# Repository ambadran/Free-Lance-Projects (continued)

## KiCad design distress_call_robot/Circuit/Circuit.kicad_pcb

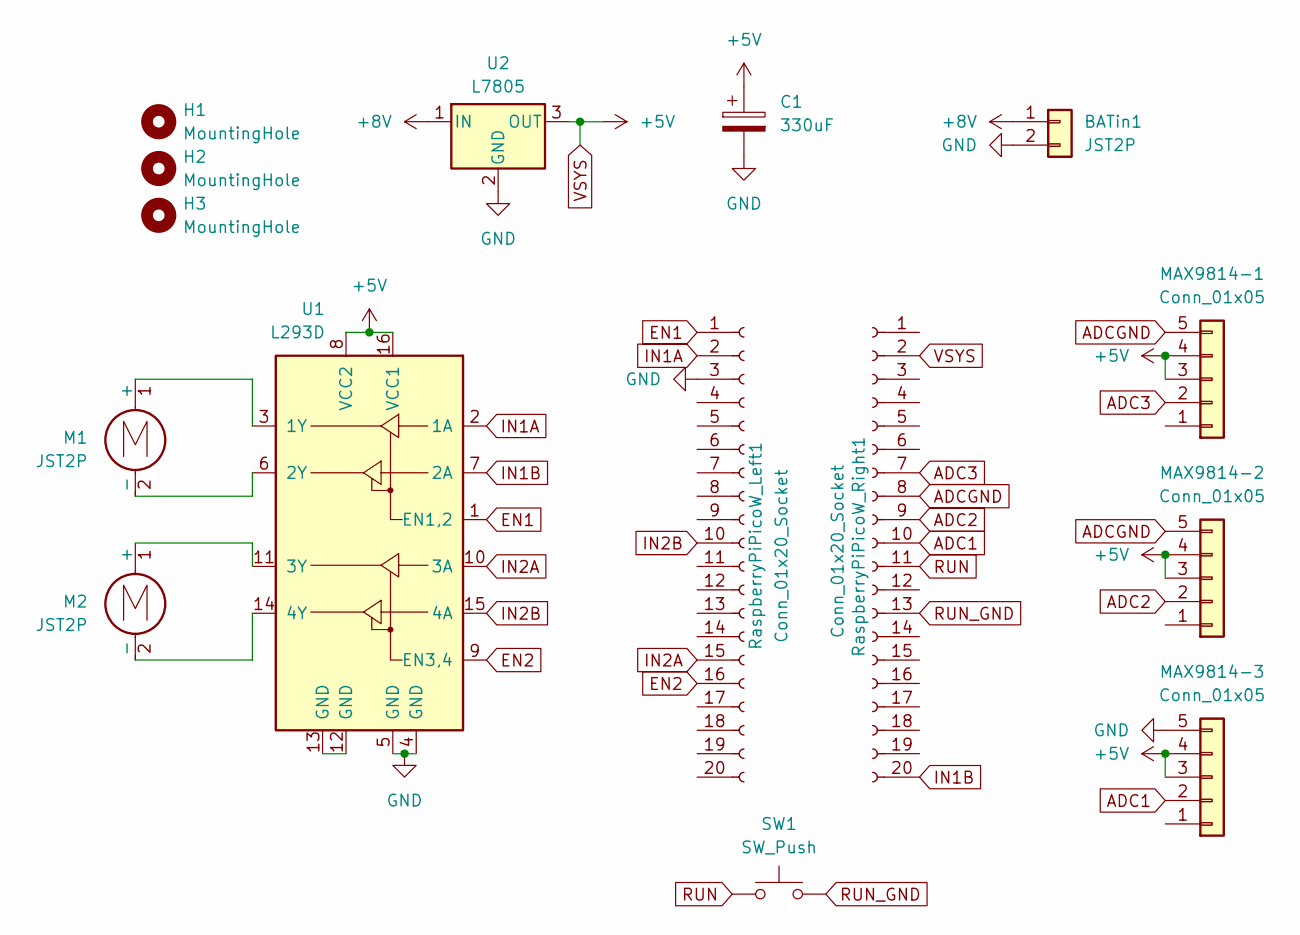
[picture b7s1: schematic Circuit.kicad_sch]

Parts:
BATin1: JST2P; JST_EH_B2B-EH-A_1x02_P2.50mm_Vertical
C1: 330uF; CP_Radial_D6.3mm_P2.50mm
H1, H2, H3: MountingHole; MountingHole_3.2mm_M3_DIN965_Pad
M1, M2: JST2P; JST_EH_B2B-EH-A_1x02_P2.50mm_Vertical
MAX9814-1, MAX9814-2, MAX9814-3: Conn_01x05; PinSocket_1x05_P2.54mm_Vertical
RaspberryPiPicoW_Left1: Conn_01x20_Socket; PinHeader_1x20_P2.54mm_Vertical
RaspberryPiPicoW_Right1: Conn_01x20_Socket; PinHeader_1x20_P2.54mm_Vertical
SW1: SW_Push; R_Axial_DIN0204_L3.6mm_D1.6mm_P5.08mm_Vertical
U1: L293D; DIP-16_W7.62mm_Socket_LongPads
U2: L7805; TO-220-3_Vertical

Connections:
+8V: BATin1.1, U2.1 (IN)
ADC1: MAX9814-3.2, RaspberryPiPicoW_Right1.10
ADC2: MAX9814-2.2, RaspberryPiPicoW_Right1.9
ADC3: MAX9814-1.2, RaspberryPiPicoW_Right1.7
ADCGND: MAX9814-1.5, MAX9814-2.5, RaspberryPiPicoW_Right1.8
EN1: RaspberryPiPicoW_Left1.1, U1.1 (EN1,2)
EN2: RaspberryPiPicoW_Left1.16, U1.9 (EN3,4)
GND: BATin1.2, C1.2, MAX9814-3.5, RaspberryPiPicoW_Left1.3, U1.4 (GND), U1.5 (GND), U2.2 (GND)
IN1A: RaspberryPiPicoW_Left1.2, U1.2 (1A)
IN1B: RaspberryPiPicoW_Right1.20, U1.7 (2A)
IN2A: RaspberryPiPicoW_Left1.15, U1.10 (3A)
IN2B: RaspberryPiPicoW_Left1.10, U1.15 (4A)
unnamed: M1.1 (+), U1.3 (1Y)
unnamed: M1.2 (-), U1.6 (2Y)
unnamed: M2.1 (+), U1.11 (3Y)
unnamed: M2.2 (-), U1.14 (4Y)
unnamed: U1.12 (GND), U1.13 (GND)
RUN: RaspberryPiPicoW_Right1.11, SW1.1
RUN_GND: RaspberryPiPicoW_Right1.13, SW1.2
VSYS: C1.1, MAX9814-1.3, MAX9814-1.4, MAX9814-2.3, MAX9814-2.4, MAX9814-3.3, MAX9814-3.4, RaspberryPiPicoW_Right1.2, U1.8 (VCC2), U1.16 (VCC1), U2.3 (OUT)

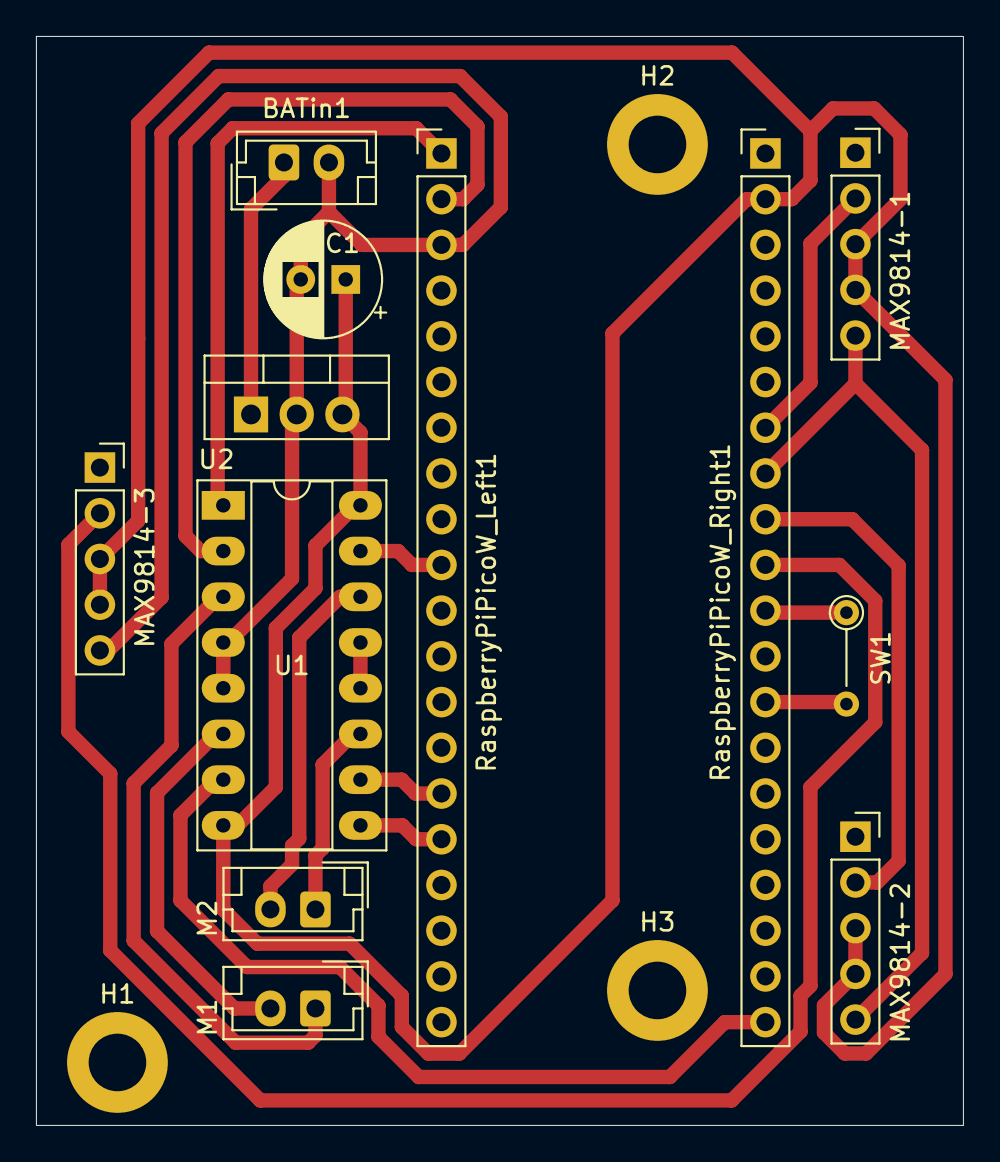
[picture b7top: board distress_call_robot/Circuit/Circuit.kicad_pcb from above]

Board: 2 copper layers, 51.5 x 60.5 mm, 15 parts (0 on the bottom side), 20 nets.

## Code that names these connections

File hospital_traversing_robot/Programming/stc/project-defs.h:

#ifndef PROJECT_DEFS_H
#define PROJECT_DEFS_H

/* gpio-hal Settings */
#define EnA_PORT GPIO_PORT2 // initiated by advpwm
#define EnA_PIN GPIO_PIN1  // initiated by advpwm
#define EnB_PORT GPIO_PORT3  // initiated by advpwm
#define EnB_PIN GPIO_PIN4  // initiated by advpwm
#define IN1_PORT GPIO_PORT2
#define IN1_PIN GPIO_PIN0
#define IN2_PORT GPIO_PORT3
#define IN2_PIN GPIO_PIN7
#define IN3_PORT GPIO_PORT3
#define IN3_PIN GPIO_PIN5
#define IN4_PORT GPIO_PORT3
#define IN4_PIN GPIO_PIN6

#define NRF24_CSN_PORT GPIO_PORT2 
#define NRF24_CSN_PIN GPIO_PIN2
#define NRF24_MOSI_PORT GPIO_PORT2  // iniated by spi-hal
#define NRF24_MOSI_PIN GPIO_PIN3  // iniated by spi-hal
#define NRF24_MISO_PORT GPIO_PORT2  // iniated by spi-hal
#define NRF24_MISO_PIN GPIO_PIN4  // iniated by spi-hal
#define NRF24_SCLK_PORT GPIO_PORT2  // iniated by spi-hal
#define NRF24_SCLK_PIN GPIO_PIN5  // iniated by spi-hal
#define NRF24_CE_PORT GPIO_PORT2  
#define NRF24_CE_PIN GPIO_PIN6  

#define HCSR04_TRIGGER_PORT GPIO_PORT3
#define HCSR04_TRIGGER_PIN GPIO_PIN2
#define HCSR04_ECHO_PORT GPIO_PORT3
#define HCSR04_ECHO_PIN GPIO_PIN3

#define NEO_M8N_PORT GPIO_PORT1
#define NEO_M8N_RX_PIN GPIO_PIN0
#define NEO_M8N_TX_PIN GPIO_PIN1

#define LED_PORT GPIO_PORT1
#define LED_PIN GPIO_PIN3

/* uart-hal Settings */
#define HAL_UARTS 2
#define UART2_RX_BUFFER_SIZE 233 //MUST DO THIS TO RECEIVE ALL NMEA STATEMENT!

#define CONSOLE_SPEED 250000
#define CONSOLE_UART UART1
#define CONSOLE_PIN_CONFIG 0  // TX->P3.1, RX->P3.0

#define NEO_M8N_UART_SPEED 9600
#define NEO_M8N_UART UART2
#define NEO_M8N_UART_PIN_CONFIG 0  // TX->P1.1, RX->P1.0

/* pwm Settings */
#define HAL_PWM_CALCULATE_PARAMETERS
#define HAL_PWM_NO_COUNTER_INT_HANDLER
#define HAL_PWM_NO_CHANNEL_INT_HANDLER
// EnA pin is P2.1/PWM1N_2
#define PWM_MOTOR_RIGHT_COUNTER PWM_COUNTER_A
#define PWM_MOTOR_RIGHT_CHANNEL PWM_Channel0
#define PWM_MOTOR_RIGHT_PIN_CONFIG 1
#define PWM_MOTOR_RIGHT_OUTPUT_MODE PWM_OUTPUT_N_ONLY 
// EnB in is P3.4/PWM4P_4/PWM8_2
#define PWM_MOTOR_LEFT_COUNTER PWM_COUNTER_B
#define PWM_MOTOR_LEFT_CHANNEL PWM_Channel7
#define PWM_MOTOR_LEFT_PIN_CONFIG 1
#define PWM_MOTOR_LEFT_OUTPUT_MODE PWM_OUTPUT_P_ONLY


/* timer-hal configs */
#define HAL_TIMER_API_STOP_TIMER
// Timer assignments
#define GLOBAL_TIMER TIMER0
#define GLOBAL_TIMER_ISR timer0_isr
#define GLOBAL_TIMER_INTERRUPT TIMER0_INTERRUPT
// TIMER1 is used for CONSOLE_UART
#define NEO_M8N_TIMER UART_USE_OWN_TIMER // TIMER2 is used for UART2
#define HCSR04_TIMER TIMER4
#define HCSR04_TIMER_ISR timer4_isr
#define HCSR04_TIMER_INTERRUPT TIMER4_INTERRUPT

/* external pin interrupts */
#define HCSR04_INT_PIN_ISR extint1_isr  // ECHO Pin, P3.3
#define HCSR04_INT_PIN_INTERRUPT EXTINT1_INTERRUPT // ECHO Pin, P3.3

/* SPI settings */
#define SPI_PIN_CONFIG 1
/* #define SPI_SPEED 8000000 */
#define SPI_SPEED 4000000UL

/* I2C settings */
#define CHOOSEN_I2C_PIN_SWITCH 0

/* nRF24L01 settings */
//#define NRF_DEBUGGING  //uncomment to print all the nrf24l01 registers after setting them with nrf24_device()
#define RF_CHANNEL_DEFAULT 46

/* HC05 Sensor Settings*/
#define ULTRASONIC_DEBUG
#define HCSR04_TIMER_COUNTER_TO_CM  233 //TODO: actually calculate and get this value
#define HCSR04_READ_PERIOD_MS 500


/* MPU6050 Settings */
// #define TEST_MPU_ACCEL  // If this setting is enabled the MCU will do nothing but keep printing the MPU values
// #define TEST_MPU_GYRO
#define ACCEL_SCALE 1000  // fixed-point value instead of floating point, 
#define ACCEL_SENSITIVITY ACCEL_SENSITIVITY_0  // 16-bit range is divided into max 2g
#define GYRO_SENSITIVITY GYRO_SENSITIVITY_0  // 16-bit range is divided into max 500deg/sec
//TODO: These values are set in place and no calibration routine yet
#define DEFAULT_ACCEL_OFFSET_X 0
#define DEFAULT_ACCEL_OFFSET_Y 0
#define DEFAULT_ACCEL_OFFSET_Z 0
//NOTE: gyro offset is calculated with every power up using a calibration routine
#define DEFAULT_GYRO_OFFSET_X 0
#define DEFAULT_GYRO_OFFSET_Y 0
#define DEFAULT_GYRO_OFFSET_Z 0
#define GYRO_CALIBRATION_SAMPLES 1000
#define GYRO_DT 10

/* HMC5883L settings */
/* #define TEST_MPU_MAG */
#define DEFAULT_MAG_GAIN HMC5883L_GAIN_1090
#define DEFAULT_MAG_OFFSET_X 0
#define DEFAULT_MAG_OFFSET_Y 0
#define DEFAULT_MAG_OFFSET_Z 0

/* NEO M8N Settings */

/* Differential Control Settings */
#define CM_TO_MOVEMENT_MS 15  // 1cm is moved in CM_TO_MOVEMENT_MS
#define DEGREE_TO_MOVEMENT_MS 3 // 1 degree is moved in DEGREE_TO_MOVEMENT_MS
#define PWM_MOTOR_FREQ 10000
#define DEFAULT_PWM_DUTY_CYCLE 50000  // The range is (0-2^16)

/* Orientation HAL settings */
#define COMP_FILTER_DT 30
#define COMP_FILTER_ALPHA 30  // %
#define COMP_FILTER_BETA  (100-COMP_FILTER_ALPHA) 
// Getting the orientation can be done through multitude of ways.
// for example roll could be derived from only accelerometer or only gyroscope or sensor fuse both
// The next setting specifies how each orientation: ROLL, PITCH, YAW is derived
// This allows flexible orientation aquiring and test the different advantages of each method
#define orientation_get_roll_deg get_accel_roll_deg
#define orientation_get_pitch_deg get_accel_pitch_deg
#define orientation_get_yaw_deg get_gyro_yaw_deg
// very important if no absolute yaw measurement procedure is implemented
#define STARTING_YAW_VALUE WEST
#define YAW_MULTIPLE_COMPENSATE 2.5

/* Closed loop Control Settings */
#define TOTAL_ORIENT_TIMEOUT_MS 10000         // Max time for entire operation (10 seconds)
#define TOTAL_MOVE_TIMEOUT_MS 20000         // Max time for entire operation (20 seconds)
#define DEG_TOLERANCE 1                // Acceptable error in degrees
#define CM_TOLERANCE 1                // Acceptable error in CM
#define MINIMUM_YAW_CHANGE 1               // Minimum detectable yaw change (degrees)
#define MINIMUM_DISTANCE_CHANGE 1               // Minimum detectable yaw change (degrees)
#define STUCK_ORIENT_TIMEOUT_MS 200          // Max time without sufficient change
#define STUCK_DISTANCE_TIMEOUT_MS 200          // Max time without sufficient change
#define OVERSHOOT_ORIENT_PERCENT 250           // 200% overshoot (integer percentage)
#define OVERSHOOT_MOVE_PERCENT 50           // 50% overshoot (integer percentage)

/* Advanced Movements Settings */
/* #define ADV_MOVEMENT_DEBUG */
#define EXIT_ROOM_DISTANCE 10
#define ENTER_ROOM_DISTANCE 10
#define CORRIDOR_MOVEMENT_DISTANCE 10
#define RAMP_ANGLE 30

/* Path Planning Settings */
/* #define PATH_PLANNING_DEBUG */

// Others 
/* #define GPIO_HAS_INT_WK */
#define LED_BLINK_PERIOD 400

#include <STC/8H8KxxU/SKDIP28.h>
#include <stdio.h>
#include <stdlib.h>
#include <stdint.h>
#include <string.h>
#include <stdarg.h>
#include <math.h>
#include <delay.h>
#include <gpio-hal.h>
#include <timer-hal.h>
#include <uart-hal.h>
#include <serial-console.h>
#include <spi-hal.h>
#include <i2c-hal.h>
#include <advpwm-hal.h>
#include "global_timer.h"
#include "report.h"
#include "nrf24l01.h"
#include "differential_control.h"
#include "neo_m8n.h"
#include "hc_sr04.h"
#include "mpu6050.h"
#include "hmc5883l.h"
#include "orientation.h"
#include "closed_loop_movements.h"
#include "adv_movement.h"
#include "path_planning.h"
#include "terminal.h"
#include "protocol.h"

#endif

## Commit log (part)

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2024-06-29 added smart watch files
2024-06-29 file restructuring
2024-07-01 finished smart watch project, data read, parsed and sent to firebase successfully
2024-07-01 minor changes in smart watch project
2024-07-07 added smart product display base project
2024-07-07 finished sensor and led interfacing, pending video playing logic
2024-07-08 tested Power circuit and finished most PCB layout
2024-07-10 finished PCB layout
2024-07-10 modified script pin assignments
2024-07-10 added video selection algorithm
2024-07-23 added smoke detector project
2024-07-30 finished led sign project
2024-07-30 minor changes to smart product display project
2024-07-31 minor changes in led sign BOM
2024-07-31 started new led sign circuit
2024-08-04 minor changes
2024-08-05 added small power supply project
2024-08-07 added line follower robot code
2024-08-24 final line follower robot file changes
2024-08-24 added hoverboard wifi control project
2024-09-12 added Product linear motion view BOM
2024-09-12 finished 3d modelling
2024-09-14 added menu screen project
2024-09-18 added relay control board project
2024-10-30 added unipolar arduino driver project
2024-10-30 finished unipolar driver
2024-11-02 added unipolar driver BOM
2024-11-05 finished unipolar driver project
2024-11-06 added new projects
2024-11-06 added incubator to to here
2024-11-08 modified unipolar driver and further development in distress call robot
2024-11-10 further dev in distress call robot
2024-11-10 further dev in distress robot
2024-11-13 changed sound data to bytearrays!
2024-11-14 adc value from pico to .wav file on pc through wifi finished
2024-11-16 added BOM and started circuit design
2024-11-18 finished distress robot PCB and DC motor differential control code
2024-11-19 added web controlled 48 relay Project
2024-11-21 finished all backend of web controled 48 relay project
2024-11-23 finished GUI web controlled 48 relay
2024-11-24 further dev
2024-11-24 further development in web controlled relay project
2024-11-25 finished manual/automatic mode of esp32 connection relay control project
2024-11-27 fixed reliability issues in relay control and created windows executable
2024-11-27 added relay memory feature
2024-11-29 modified BOM
2024-12-01 finished GPS, distress call code and many more
2024-12-03 added stepper motor controller project
2024-12-05 added ultrasonic and PIR functionality as well as performance increased
2024-12-05 stepper motor controller circuit moredevelopment and started the programming
2024-12-10 finished buttons switches and encoder interfacing for stepper driver
2024-12-11 added stepper motor driver and finished PCB
2024-12-13 huge progress in programming in stepper_motor_controller project
2024-12-14 further development in application layer of stepper controller project
2024-12-14 finished stepper_motor_control Project
2024-12-15 started wind sensor project
2024-12-17 finished glucometer project
2024-12-18 added digit precise revolution control and external relay RUN terminals
2024-12-24 started keyboard emulator project and updated wind sensor code
2024-12-25 started rc rover project
2024-12-25 finished circuit schematic and PCB layout
2024-12-25 Finished initial Code structuring and architecture
2024-12-25 further dev in circuit and programming of keyboard emulator
2024-12-26 finished keyboard emulator circuit and some BOMs
2024-12-26 finished wind sensor code
2024-12-27 further development in rc rover programming
2024-12-28 added light sensor code, finished wind sensor project
2024-12-28 Code restructuring
2024-12-29 finished keyboard emulator project
2024-12-29 Started rc rover Programming
2025-01-01 finished 8088 and bts7960 interfacing projtects
2025-01-04 finally made successful SPI connection to nrf in rc rover Project
2025-01-05 further dev in rc rover programming
2025-01-07 removed stepper motor controller project to have its own repo
2025-01-21 added step files for keyboard emulator
2025-01-24 trying to debug the stupid nrf
2025-01-25 further failure
2025-01-27 started product display stepper speaker project
2025-02-05 started product stepper speaker project
2025-02-06 finished circuit schematic and started pcb layout of product speaker stepper project
2025-02-07 almost finished pcb layout solution
2025-02-09 finished circuits of both hospital rover and product display with speakers and steppers projects
2025-02-09 finished ordering and BOM
2025-02-10 major circuit fixing for both current projects
2025-02-11 started programming product display stepper speaker project
2025-02-12 added circuit step files for both current projects
2025-02-12 almost finished product display project programming
2025-02-18 finished and tested stepper hal layer of product display speaker stepper project
2025-02-25 started V2 of this project, gonna use Pico w instead of esp-12e
2025-02-27 started programming hospital robot Main board
2025-03-06 started station circuit in hospital rover project
2025-03-06 finished station circuit PCB and started V2 product display stepper speaker circuit
2025-03-08 finished product display stepper speaker circuit V2 PCB layout and generated gerber files and PDFs
2025-03-11 updated current circuits to new kicad version
2025-03-19 started station programming
2025-04-12 further development in hospital rover project
2025-04-13 hospital rover stc programming
2025-04-15 further development in mpu6050 in hospital rovoer
2025-04-16 further development in mpu6050
2025-04-16 further development in mpu6050 driver
2025-04-17 minor bug fix
2025-04-17 further dev in mpu6050
2025-04-18 added back pwm functionality and finished gyro calibration
2025-04-19 finished implementing PWM on hospital rover
2025-04-20 added step files
2025-04-21 finally fixed reliability bug in nrf24 communication
2025-04-24 finished getting raw offseted fixed-point values from IMU
2025-04-25 further devlepment for mpu
2025-04-26 finish an extremely efficient implementation of roll/pitch finding using MPU6050 while still maintaining accuracy
2025-04-27 finshed mpu6050, roll and pitch measurement and started hmc5883l interfacing
2025-04-27 hmc5883l finished responsiveness test successfully
2025-04-28 further development in HMC5883L library
2025-04-28 finished function implementation of hmc5883l
2025-04-28 Finally I can pull uT values from magnetometer :D
2025-05-12 added true pitch and roll calculations with (1ms time)
2025-05-19 further dev in yaw implementation from hmc5883
2025-05-22 started developing path planning algorithm
2025-06-04 finished path planning of hospital rover using BFS algorithm
2025-06-05 started closed loop movements
2025-06-07 Finished HC05 ultrasonic sensor real-time implementation
2025-06-07 bug fix in new ultrasonic implementation
2025-06-09 finished path planning to closed loop function mapping, use gyro to get yaw angle instead of unreliable magnetometer. lots and lots of bug fixes
2025-06-10 finished new high level closed loop implementation
2025-06-11 finished first closed function completely, pending duplicate logic for the rest ;)
2025-06-12 futher development in closed loop control
2025-06-13 finally finished and tested closed loop control algorithm fully
2025-06-13 further dev in micropython
2025-06-13 bug fix in station implementation
2025-06-14 finished proper micropython abstraction to control all developed features of STC robot
2025-06-14 added closed loop move func
2025-06-15 further development of backend of web app hosting
2025-06-19 almost finished web app and almost finished final advanced movement of robot
2025-06-20 finished advanced movement component and some fine tuning
2025-06-23 started new project web controlled relay board v2.0
2025-07-16 finished circuit schematic of relay board v2.0
2025-07-17 PCB finished, pending final touches
2025-07-18 finished final touches of PCB schematic and layout
2025-07-23 added BOM
2025-07-23 updated desktop app and finished micropython
2025-07-27 bug fixes and added docs
2025-07-27 added windows executable
2025-08-03 added seperate led file
2025-08-03 added new features requested by user
2025-08-03 finished v2.0 desktop app and micropython
2025-08-10 added full license version
